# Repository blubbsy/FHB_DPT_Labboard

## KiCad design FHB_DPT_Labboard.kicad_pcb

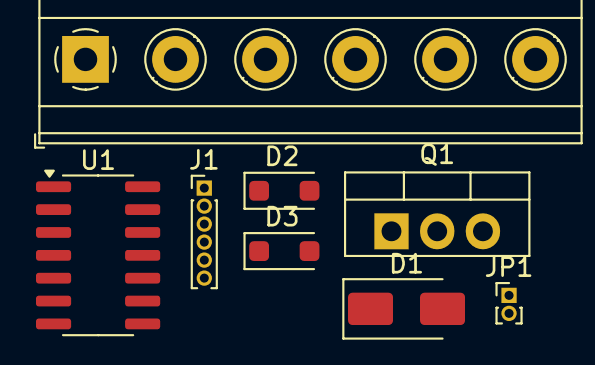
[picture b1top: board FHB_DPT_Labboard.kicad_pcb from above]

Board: 2 copper layers, 8 parts (0 on the bottom side), 9 nets, no tracks yet.

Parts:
D1: US1J; D_SMA
D2, D3: PMEG3020EH; D_SOD-123F
J1: Conn_01x06; PinHeader_1x06_P1.00mm_Vertical
J2: Conn_01x06; TerminalBlock_Phoenix_MKDS-1,5-6_1x06_P5.00mm_Horizontal
JP1: Jumper_2_Bridged; PinHeader_1x02_P1.00mm_Vertical
Q1: STGP7NC60HD; TO-220-3_Vertical
U1: L6491; SO-14_3.9x8.65mm_P1.27mm

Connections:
/LIN: J1.5, J2.5
/PWM_H: J1.6, J2.6
/PWM_L: J1.3, J2.3
GNDPWR: JP1.2 (B), U1.7 (PGND)
GNDS: J1.1, J2.1, JP1.1 (A), U1.6 (SGND)
unnamed: D1.1 (K), U1.14 (BOOT)
unnamed: D2.2 (A), Q1.1 (G)
unnamed: Q1.3 (E), U1.12 (OUT)
VCC: J1.2, J2.2, U1.4 (VCC)

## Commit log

2024-07-11 init
2024-07-15 Înitial design for DPT PCB.
